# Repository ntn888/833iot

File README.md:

# 833iot

**UNTESTED**
based off [nRFMicro](https://github.com/joric/nrfmicro)

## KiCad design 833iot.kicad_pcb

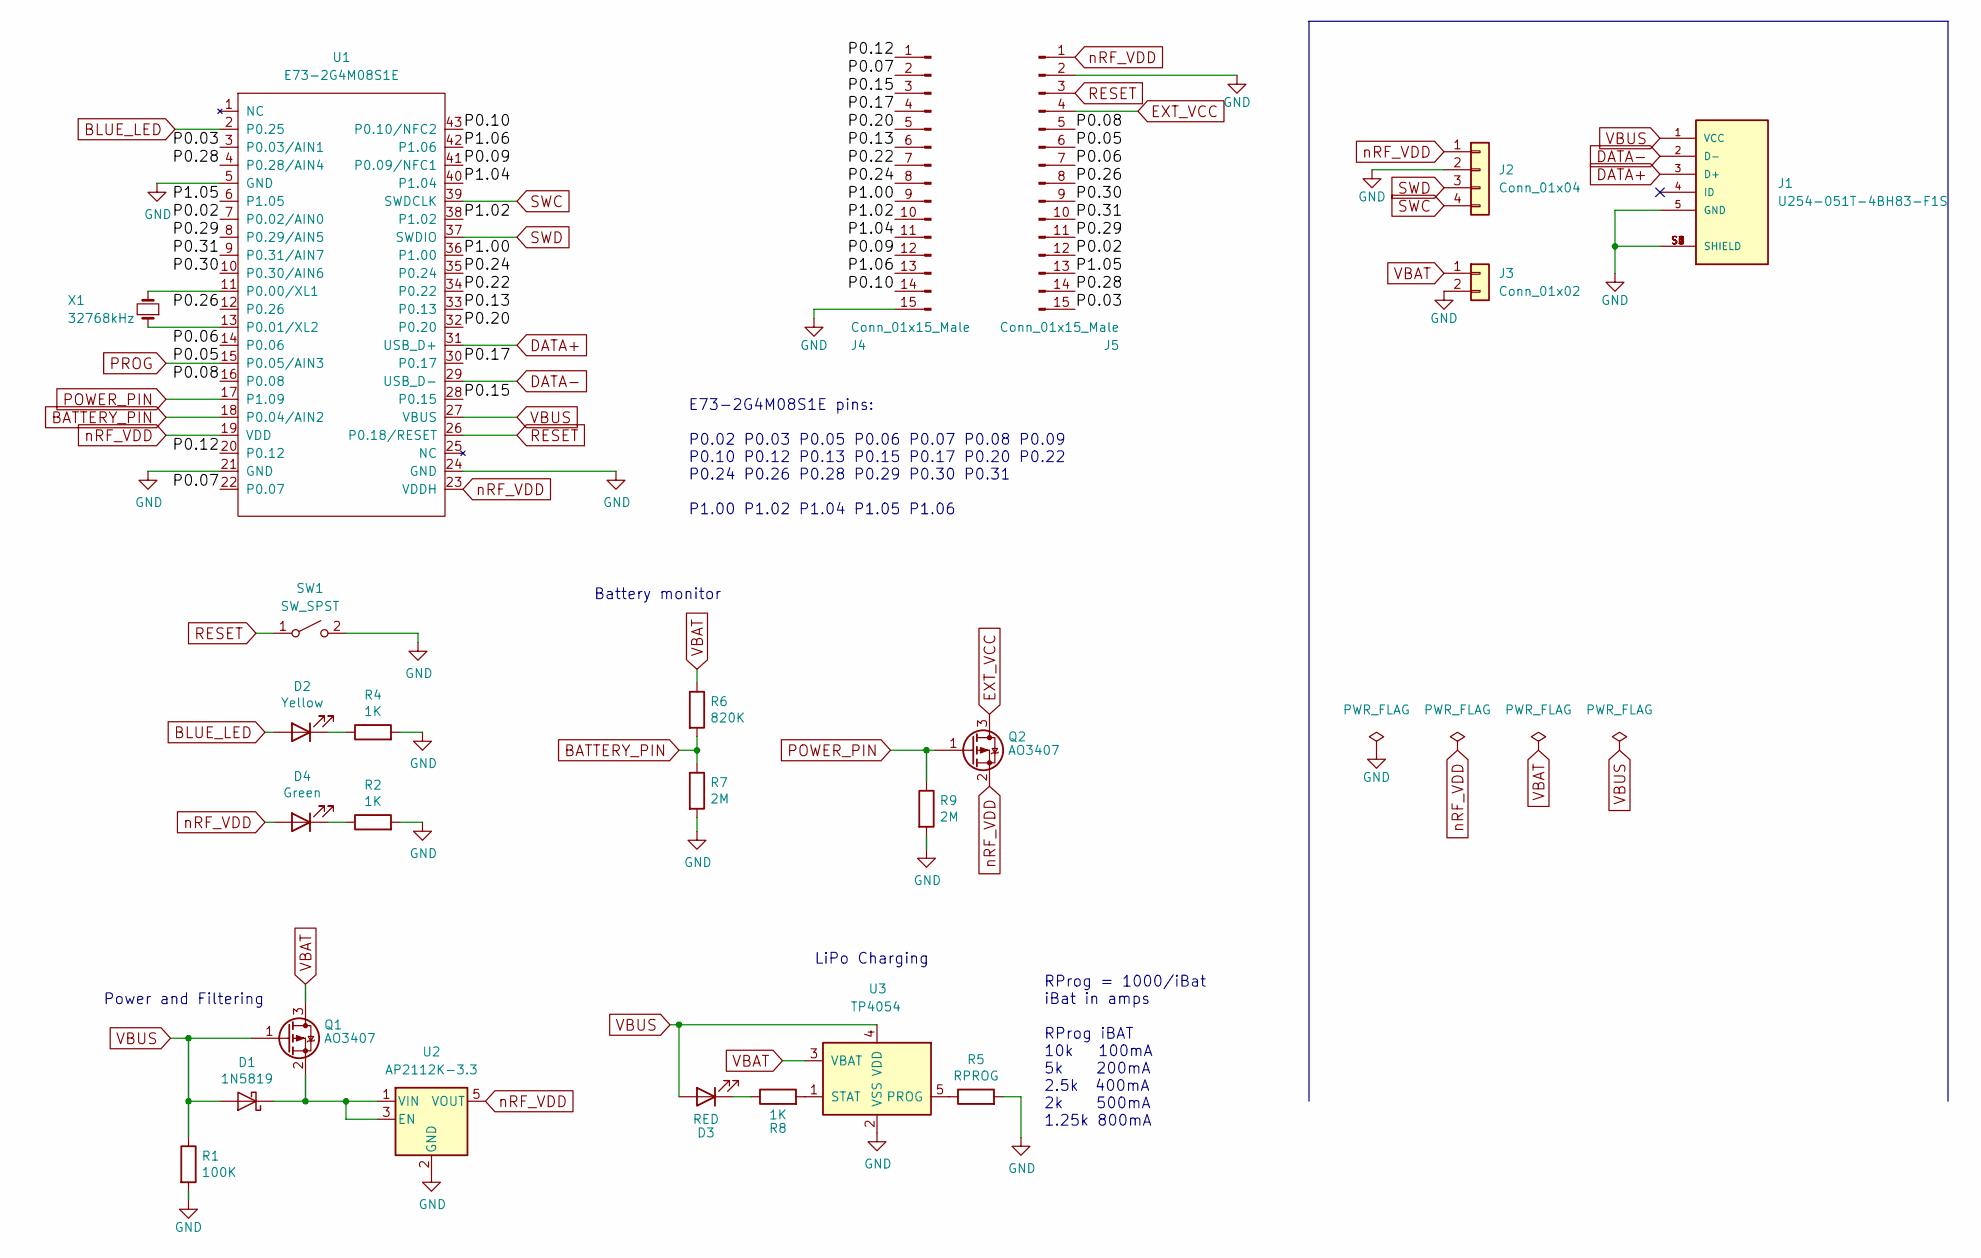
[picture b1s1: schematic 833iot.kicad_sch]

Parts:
D1: 1N5819; D_SOD-323F; LCSC Part # C440261
D2: Yellow; LED_0603_1608Metric; LCSC Part # C74343
D3: RED; LED_0603_1608Metric; LCSC Part # C253533
D4: Green; LED_0603_1608Metric; LCSC Part # C181862
J1: U254-051T-4BH83-F1S; XKB_U254-051T-4BH83-F1S; PARTREV A0; LCSC Part # C397452
J2: Conn_01x04; connector_swd
J3: Conn_01x02; connector_bat
J4, J5: Conn_01x15_Male; PinHeader_1x15_P2.54mm_Vertical
Q1, Q2: AO3407; SOT-23; LCSC Part # C181093
R1: 100K; R_0603_1608Metric; LCSC Part # C269682
R2, R4, R8: 1K; R_0603_1608Metric; LCSC Part # C269704
R5: RPROG; R_0603_1608Metric; LCSC Part # C2096417
R6: 820K; R_0603_1608Metric; LCSC Part # C218156
R7, R9: 2M; R_0603_1608Metric; LCSC Part # C26102
SW1: SW_SPST; SW_SPST_TL3342; LCSC Part # C318884
U1: E73-2G4M08S1E; E73-2G4M08S1C-52840; LCSC Part # C2903762
U2: AP2112K-3.3; SOT-23-5; LCSC Part # C51118
U3: TP4054; SOT-23-5; LCSC Part # C668215
X1: 32768kHz; Crystal_SMD_3215-2Pin_3.2x1.5mm; LCSC Part # C130253

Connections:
/P0.02: J5.12, U1.7 (P0.02/AIN0)
/P0.03: J5.15, U1.3 (P0.03/AIN1)
/P0.06: J5.7, U1.14 (P0.06)
/P0.07: J4.2, U1.22 (P0.07)
/P0.08: J5.5, U1.16 (P0.08)
/P0.09: J4.12, U1.41 (P0.09/NFC1)
/P0.10: J4.14, U1.43 (P0.10/NFC2)
/P0.12: J4.1, U1.20 (P0.12)
/P0.13: J4.6, U1.33 (P0.13)
/P0.15: J4.3, U1.28 (P0.15)
/P0.17: J4.4, U1.30 (P0.17)
/P0.20: J4.5, U1.32 (P0.20)
/P0.22: J4.7, U1.34 (P0.22)
/P0.24: J4.8, U1.35 (P0.24)
/P0.26: J5.8, U1.12 (P0.26)
/P0.28: J5.14, U1.4 (P0.28/AIN4)
/P0.29: J5.11, U1.8 (P0.29/AIN5)
/P0.30: J5.9, U1.10 (P0.30/AIN6)
/P0.31: J5.10, U1.9 (P0.31/AIN7)
/P1.00: J4.9, U1.36 (P1.00)
/P1.02: J4.10, U1.38 (P1.02)
/P1.04: J4.11, U1.40 (P1.04)
/P1.05: J5.13, U1.6 (P1.05)
/P1.06: J4.13, U1.42 (P1.06)
BATTERY_PIN: R6.2, R7.1, U1.18 (P0.04/AIN2)
BLUE_LED: D2.2 (A), U1.2 (P0.25)
DATA+: J1.3 (D+), U1.31 (USB_D+)
DATA-: J1.2 (D-), U1.29 (USB_D-)
EXT_VCC: J5.4, Q2.3 (D)
GND: J1.5 (GND), J1.S1 (SHIELD), J1.S2 (SHIELD), J1.S3 (SHIELD), J1.S4 (SHIELD), J1.S5 (SHIELD), J1.S6 (SHIELD), J2.2, J3.2, J4.15, J5.2, R1.2, R2.2, R4.2, R5.2, R7.2, R9.2, SW1.2 (B), U1.5 (GND), U1.21 (GND), U1.24 (GND), U2.2 (GND), U3.2 (VSS)
unnamed: D1.1 (K), Q1.2 (S), U2.1 (VIN), U2.3 (EN)
unnamed: D2.1 (K), R4.1
unnamed: D3.1 (K), R8.1
unnamed: D4.1 (K), R2.1
unnamed: R5.1, U3.5 (PROG)
unnamed: R8.2, U3.1 (STAT)
unnamed: U1.11 (P0.00/XL1), X1.2
unnamed: U1.13 (P0.01/XL2), X1.1
POWER_PIN: Q2.1 (G), R9.1, U1.17 (P1.09)
PROG: J5.6, U1.15 (P0.05/AIN3)
RESET: J5.3, SW1.1 (A), U1.26 (P0.18/RESET)
SWC: J2.4, U1.39 (SWDCLK)
SWD: J2.3, U1.37 (SWDIO)
VBAT: J3.1, Q1.3 (D), R6.1, U3.3 (VBAT)
VBUS: D1.2 (A), D3.2 (A), J1.1 (VCC), Q1.1 (G), R1.1, U1.27 (VBUS), U3.4 (VDD)
nRF_VDD: D4.2 (A), J2.1, J5.1, Q2.2 (S), U1.19 (VDD), U1.23 (VDDH), U2.5 (VOUT)

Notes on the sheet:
LiPo Charging
RProg = 1000/iBat iBat in amps RProg iBAT 10k 100mA 5k 200mA 2.5k 400mA 2k 500mA 1.25k 800mA
Power and Filtering
Battery monitor
E73-2G4M08S1E pins: P0.02 P0.03 P0.05 P0.06 P0.07 P0.08 P0.09 P0.10 P0.12 P0.13 P0.15 P0.17 P0.20 P0.22 P0.24 P0.26 P0.28 P0.29 P0.30 P0.31 P1.00 P1.02 P1.04 P1.05 P1.06

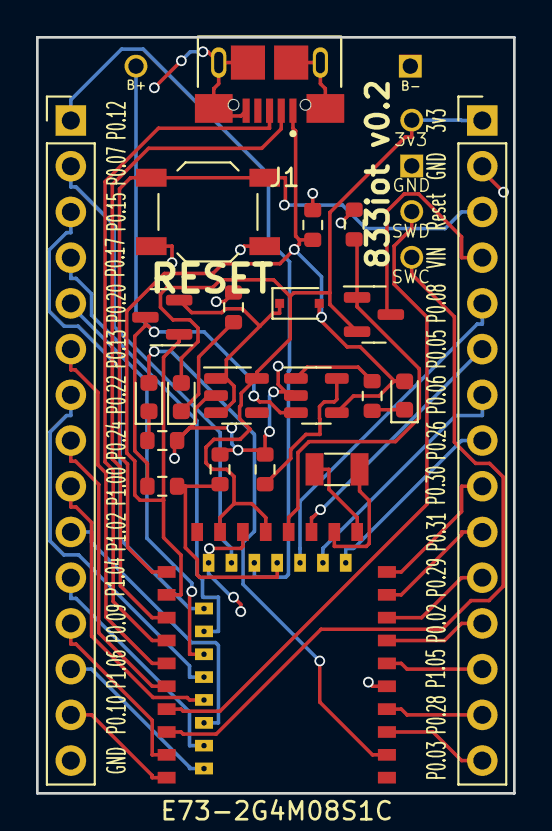
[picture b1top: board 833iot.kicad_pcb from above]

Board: 2 copper layers, 26.5 x 42.0 mm, 24 parts (0 on the bottom side), 46 nets.

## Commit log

2022-03-23 add license
2022-03-23 add origin in readme
2022-03-24 fix vias issue
